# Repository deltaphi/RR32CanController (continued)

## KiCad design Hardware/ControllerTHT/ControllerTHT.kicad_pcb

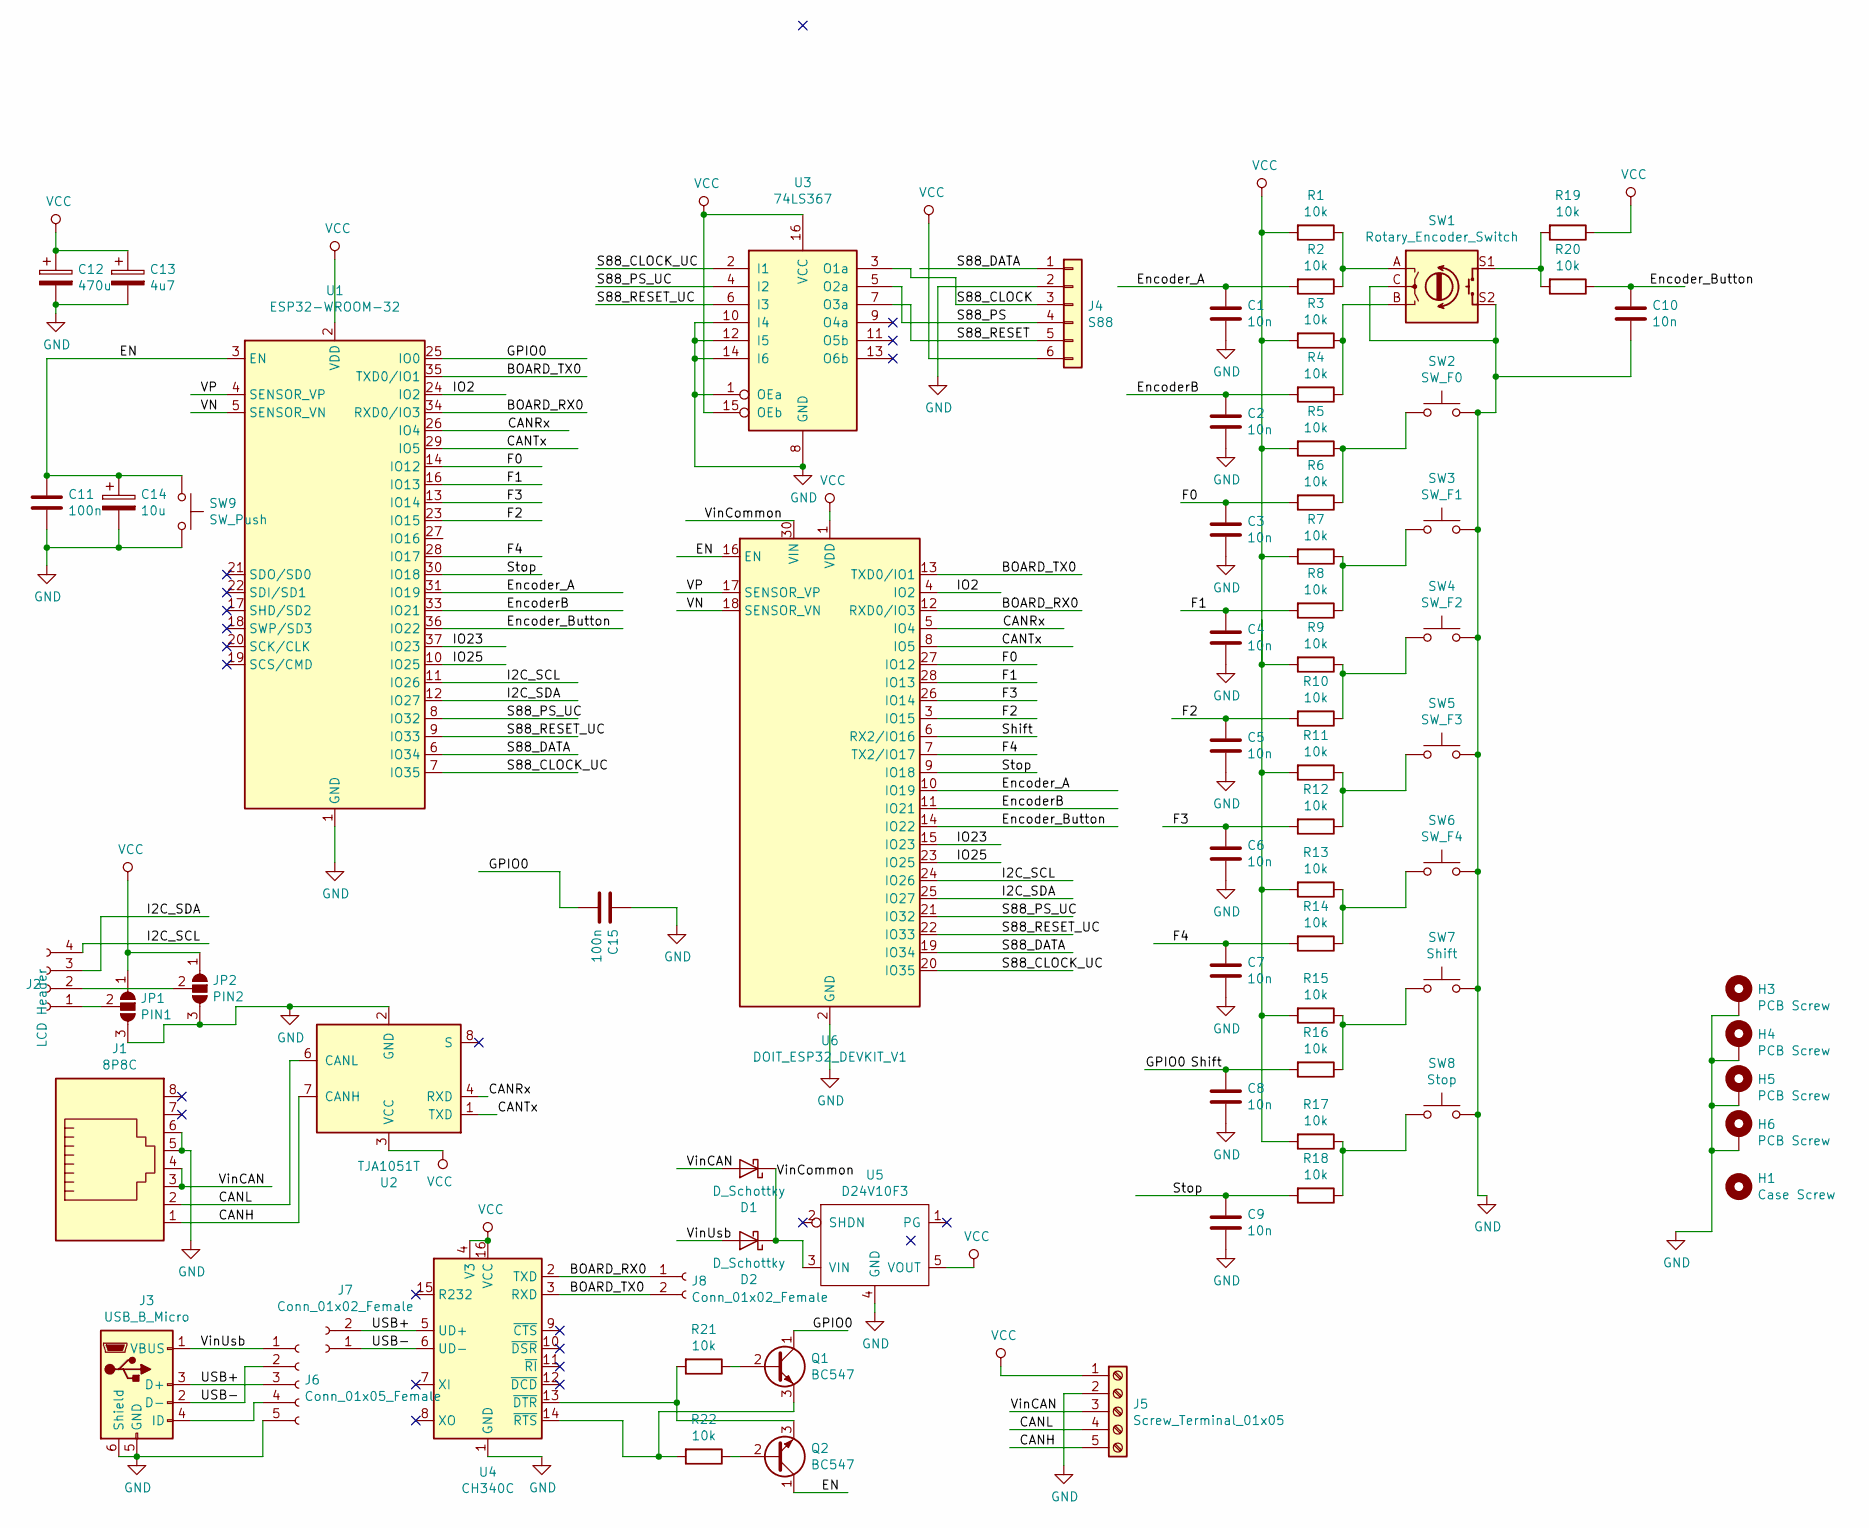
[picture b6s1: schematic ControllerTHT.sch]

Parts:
C1, C2, C3, C4, C5, C6, C7, C8, C9, C10: 10n; C_Disc_D3.4mm_W2.1mm_P2.50mm
C11, C15: 100n; C_Disc_D3.4mm_W2.1mm_P2.50mm
C12: 470u; CP_Radial_D10.0mm_P5.00mm
C13: 4u7; CP_Radial_D5.0mm_P2.50mm
C14: 10u; CP_Radial_D10.0mm_P5.00mm
D1, D2: D_Schottky; D_A-405_P7.62mm_Horizontal
H1: Case Screw; MountingHole_3.2mm_M3
H3, H4, H5, H6: PCB Screw; MountingHole_2.5mm_Pad_Via
J1: 8P8C; RJ45_Amphenol_54602-x08_Horizontal
J2: LCD Header; PinHeader_1x04_P2.54mm_Vertical
J3: USB_B_Micro; USB_Micro-B_Molex_47346-0001
J4: S88; PinHeader_1x06_P2.54mm_Horizontal
J5: Screw_Terminal_01x05; TerminalBlock_4Ucon_1x05_P3.50mm_Vertical
J6: Conn_01x05_Female; PinHeader_1x05_P2.54mm_Vertical
J7, J8: Conn_01x02_Female; PinHeader_1x02_P2.54mm_Vertical
JP1: PIN1; SolderJumper-3_P1.3mm_Open_Pad1.0x1.5mm_NumberLabels
JP2: PIN2; SolderJumper-3_P1.3mm_Open_Pad1.0x1.5mm_NumberLabels
Q1, Q2: BC547; TO-92_Inline
R1, R2, R3, R4, R5, R6, R7, R8, R9, R10, R11, R12, R13, R14, R15, R16, R17, R18, R19, R20, R21, R22: 10k; R_Axial_DIN0207_L6.3mm_D2.5mm_P10.16mm_Horizontal
SW1: Rotary_Encoder_Switch; RotaryEncoder_Alps_EC11E-Switch_Vertical_H20mm
SW2: SW_F0; SW_PUSH_6mm_H9.5mm
SW3: SW_F1; SW_PUSH_6mm_H9.5mm
SW4: SW_F2; SW_PUSH_6mm_H9.5mm
SW5: SW_F3; SW_PUSH_6mm_H9.5mm
SW6: SW_F4; SW_PUSH_6mm_H9.5mm
SW7: Shift; SW_PUSH_6mm_H9.5mm
SW8: Stop; SW_PUSH_6mm_H9.5mm
SW9: SW_Push; SW_PUSH_6mm
U1: ESP32-WROOM-32
U2: TJA1051T; SOIC-8_3.9x4.9mm_P1.27mm
U3: 74LS367; DIP-16_W7.62mm_Socket
U4: CH340C; SOIC-16_3.9x9.9mm_P1.27mm
U5: D24V10F3
U6: DOIT_ESP32_DEVKIT_V1; ESP32-DEVKITV1

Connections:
/BOARD_RX0: J8.1, U1.34 (RXD0/IO3), U4.2 (TXD), U6.12 (RXD0/IO3)
/BOARD_TX0: J8.2, U1.35 (TXD0/IO1), U4.3 (RXD), U6.13 (TXD0/IO1)
/CANH: J1.1, J5.5, U2.7 (CANH)
/CANL: J1.2, J5.4, U2.6 (CANL)
/CANRx: U1.26 (IO4), U2.4 (RXD), U6.5 (IO4)
/CANTx: U1.29 (IO5), U2.1 (TXD), U6.8 (IO5)
/EN: C11.1, C14.1, Q2.1 (C), SW9.1, U1.3 (EN), U6.16 (EN)
/EncoderB: C2.2, R4.2, U1.33 (IO21), U6.11 (IO21)
/Encoder_A: C1.2, R2.2, U1.31 (IO19), U6.10 (IO19)
/Encoder_Button: C10.2, R20.1, U1.36 (IO22), U6.14 (IO22)
/F0: C3.2, R6.2, U1.14 (IO12), U6.27 (IO12)
/F1: C4.2, R8.2, U1.16 (IO13), U6.28 (IO13)
/F2: C5.2, R10.2, U1.23 (IO15), U6.3 (IO15)
/F3: C6.2, R12.2, U1.13 (IO14), U6.26 (IO14)
/F4: C7.2, R14.2, U1.28 (IO17), U6.7 (TX2/IO17)
/GPIO0: C8.2, C15.2, Q1.1 (C), R16.2, U1.25 (IO0), U6.6 (RX2/IO16)
/I2C_SCL: J2.4, U1.11 (IO26), U6.24 (IO26)
/I2C_SDA: J2.3, U1.12 (IO27), U6.25 (IO27)
/IO2: U1.24 (IO2), U6.4 (IO2)
/IO23: U1.37 (IO23), U6.15 (IO23)
/IO25: U1.10 (IO25), U6.23 (IO25)
/S88_CLOCK: J4.3, U3.3 (O1a)
/S88_CLOCK_UC: U1.7 (IO35), U3.2 (I1), U6.20 (IO35)
/S88_DATA: J4.1, U1.6 (IO34), U6.19 (IO34)
/S88_PS: J4.4, U3.5 (O2a)
/S88_PS_UC: U1.8 (IO32), U3.4 (I2), U6.21 (IO32)
/S88_RESET: J4.5, U3.7 (O3a)
/S88_RESET_UC: U1.9 (IO33), U3.6 (I3), U6.22 (IO33)
/Stop: C9.2, R18.2, U1.30 (IO18), U6.9 (IO18)
/USB+: J3.3 (D+), J6.3, J7.2, U4.5 (UD+)
/USB-: J3.2 (D-), J6.2, J7.1, U4.6 (UD-)
/VN: U1.5 (SENSOR_VN), U6.18 (SENSOR_VN)
/VP: U1.4 (SENSOR_VP), U6.17 (SENSOR_VP)
/VinCAN: D1.2 (A), J1.3, J1.4, J5.3
/VinCommon: D1.1 (K), D2.1 (K), U5.3 (VIN), U6.30 (VIN)
/VinUsb: D2.2 (A), J3.1 (VBUS), J6.1
GND: C1.1, C2.1, C3.1, C4.1, C5.1, C6.1, C7.1, C8.1, C9.1, C10.1, C11.2, C12.2, C13.2, C14.2, C15.1, H3.1, H4.1, H5.1, H6.1, J1.5, J1.6, J3.5 (GND), J3.6 (Shield), J4.2, J5.2, J6.5, JP1.3 (B), JP2.3 (B), SW1.C, SW1.S2, SW2.2, SW3.2, SW4.2, SW5.2, SW6.2, SW7.2, SW8.2, SW9.2, U1.1 (GND), U1.15 (GND), U1.38 (GND), U2.2 (GND), U3.1 (OEa), U3.8 (GND), U3.10 (I4), U3.12 (I5), U3.14 (I6), U4.1 (GND), U5.4 (GND), U6.2 (GND), U6.29 (GND)
unnamed: J2.1, JP1.2 (C)
unnamed: J2.2, JP2.2 (C)
unnamed: J3.4 (ID), J6.4
unnamed: Q1.2 (B), R21.1
unnamed: Q1.3 (E), R22.2, U4.14 (~RTS)
unnamed: Q2.2 (B), R22.1
unnamed: Q2.3 (E), R21.2, U4.13 (~DTR)
unnamed: R1.1, R2.1, SW1.A
unnamed: R3.1, R4.1, SW1.B
unnamed: R5.1, R6.1, SW2.1
unnamed: R7.1, R8.1, SW3.1
unnamed: R9.1, R10.1, SW4.1
unnamed: R11.1, R12.1, SW5.1
unnamed: R13.1, R14.1, SW6.1
unnamed: R15.1, R16.1, SW7.1
unnamed: R17.1, R18.1, SW8.1
unnamed: R19.2, R20.2, SW1.S1
VCC: C12.1, C13.1, J4.6, J5.1, JP1.1 (A), JP2.1 (A), R1.2, R3.2, R5.2, R7.2, R9.2, R11.2, R13.2, R15.2, R17.2, R19.1, U1.2 (VDD), U2.3 (VCC), U3.15 (OEb), U3.16 (VCC), U4.4 (V3), U4.16 (VCC), U5.5 (VOUT), U6.1 (VDD)

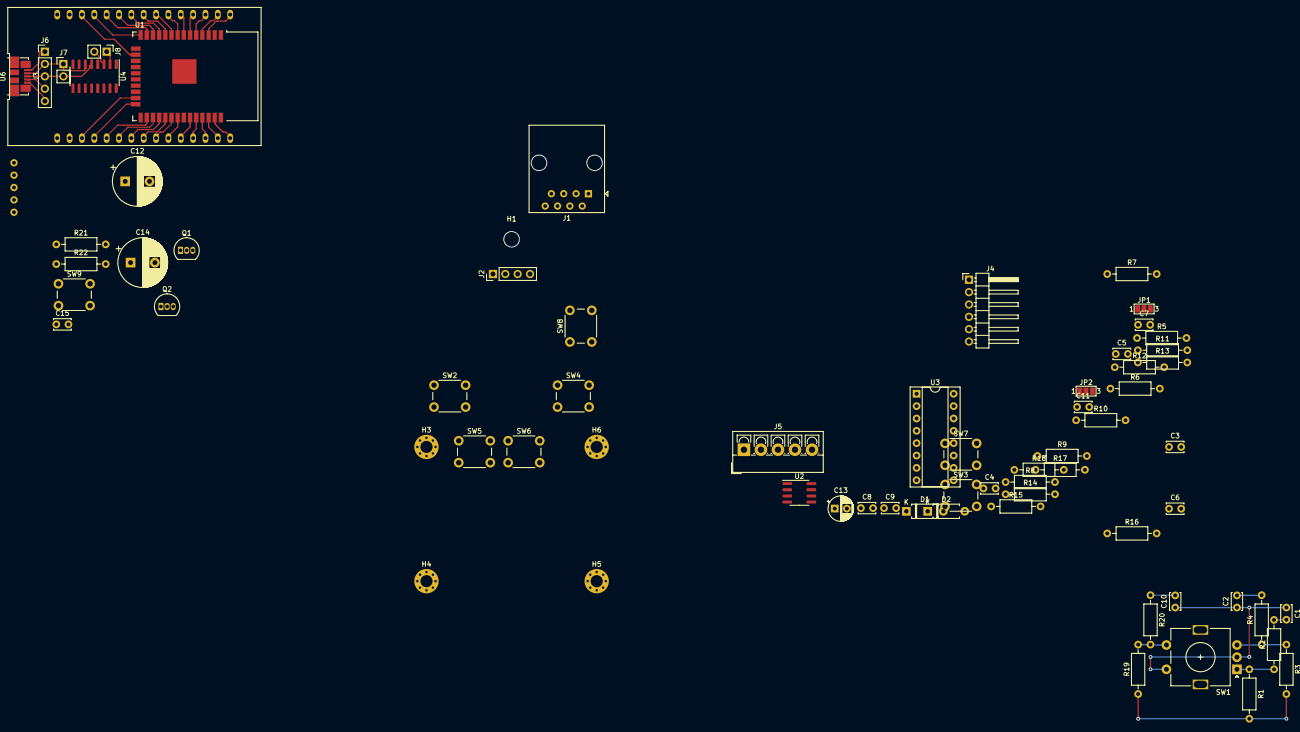
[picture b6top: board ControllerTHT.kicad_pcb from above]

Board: 2 copper layers, 71 parts (1 on the bottom side), 55 nets.

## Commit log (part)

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2018-12-30 Import of initial working prototype
2018-12-30 Fixed multi-turnouts
2019-02-07 Initial experiments with enabling the OLED display
2019-02-07 Fixed screen orientation
2019-02-07 Added RotaryEncoder Support
2019-02-13 Introduce some rudimentary structure.
2019-02-13 Display the Encoder value
2019-02-14 Fixed missing include
2019-02-14 Moved Display code to a separate class
2019-02-14 Improved output
2019-02-14 Request Loco Database
2019-02-15 Moved more code to the handler
2019-02-15 Moved sending CAN frames to the handler file
2019-02-15 Moved sending config data packets to handler
2019-02-15 Run clang-format on all the things
2019-02-16 Initial PCB
    An initial take at a PCB that can be mounted in the SP 2092 case.
    NOTE: The dimensions do not yet match!
2019-02-17 Updated fitting for SP 2090 enclosure
    Better fit, but still not perfect.
2019-02-17 Finished case-specific layout parts
2019-02-17 Added a first set of parts
2019-02-20 Added more parts
2019-02-20 Initial WiFi integration
    * Works for transmission, hardcoded to transmit via WiFi
    * Works for reception
    * Connecting to WiFi is unreliable
2019-02-21 Create an identifier from individual bytes
2019-02-21 Correctly use the send handler
2019-02-21 Fix commented code
2019-02-21 Added initial TextParser and a CMake configuration for UnitTesting
    * Downloads Google Test
    * Compiles selected sources and enables unit testing
    * Adapted apply-clang.sh to also format test case implementations
    * Initial set of bugfixes
2019-02-22 Improved BufferManager
2019-02-23 Fixed a compiler warning
2019-02-23 Initial non-working version of the TextParser
2019-02-23 Added findFirstOf for multiple characters
2019-02-23 Initial version of TextParser now working
2019-02-23 Ran clang-format
2019-02-23 Added Text parsing of incoming configuration data
    Configuration data is received and parsed. Currently, the identified tokens are dumped to the serial console only.
2019-02-24 Further renaming
2019-02-24 Added CRC functionality
2019-02-27 Added a script to create new class files
2019-02-27 Moved hash computation out of Identifier class
2019-02-27 Refactoring of types and constants
2019-02-27 Extended Identifier to allow for external hash computation
2019-02-27 Updated README with initial menuing design
2019-02-27 WIP: Added initial take on an Engine database
2019-02-28 Changed clang-format configuration to be Clang 6 compatible
    * Achieves compatibility with the build-in VS Code binary
2019-02-28 Clang-Format all the things
2019-02-28 WIP: Added more parts of the engine browser
2019-03-03 Rework on the file structure
2019-03-03 Refactoring to move parsing loknamen to other class
2019-03-03 More folder structuring
2019-03-03 Remove obsolete engine number
2019-03-03 Remove the need to erase the EngineBrowser each time
2019-03-03 Added helper function
2019-03-03 Added cursor support for the display
2019-03-03 Cursor-based browsing of engine list available
2019-03-03 Moved most message handling to Station class
2019-03-05 Switched to all-SMD Buttons
2019-03-08 Finished PCB
    * Reordered some pins to make the PCB layout easier
    * Added connector descriptions
    * Adjusted Silkscreen Items
2019-03-10 Updated USB Port
2019-03-12 Optimizations
    * Moved Screen connector to the other side
    * Optimized knee bends
2019-03-16 Fixed part footprints
2019-04-28 Made Caseness consistent
2019-04-28 Updated Gitignore
2019-04-28 Moved tests around. Set CPP standard for Tests to 17.
2019-05-19 Swap RX/TX
    Fixes #1
2019-05-26 Moved SMD controller prototype to separate folder
2019-05-26 Initial version of THT controller
2019-05-26 Added new Parts
2019-05-26 More tinkering with Footprints
2019-05-30 Intermediate steps
2019-05-30 Added an experimental ESP32 Breakout Board for Prototyping
2019-05-30 Fixup of holes and labels
2019-11-01 Improved comment
2019-11-01 Added switch for Display Flip
2019-11-01 Added default CNA pins
2019-11-01 Added preliminary support for local pushbuttons
2019-11-01 Switch menu when shift is pressed
2019-11-02 Add notification for functions
2019-11-02 UI Layout fix
2019-11-02 Improved comments
2019-11-02 Extracted Engine Direction Type
2019-11-02 Added option to conditionally set the name of the engine
    Avoids loosing the engine state in case the current engine was reselected.
2019-11-02 Extra logging
2019-11-02 Improfed end-of-stream handling
2019-11-03 Tinkered with logging
2019-11-03 Fix constant to pad with 0-bytes instead of spaces
2019-11-03 Fix requesting an engine
2019-11-03 Introduce EngineControl and initial download of Engine
2019-11-03 Fix scrolling through the engine list
2019-11-03 Fixed requesting the correct engine
2019-11-03 Removed unused variable
2019-11-03 Update to clang-format7
2019-11-04 Fix Friend Declarations
2019-11-04 More Logging
2019-11-05 Documentation improvements
2019-11-05 Removed useless includes
2019-11-05 Switch to ESP32-IDF CAN driver.
    This driver allows better buffer control.
2019-11-05 Added character push_back
2019-11-05 Added comments
2019-11-05 Run clang-format 7
2019-11-07 Display downloaded engine data
2019-11-07 Track engine speed & direction.
    Requests engine speed and direction when a new engine is selected. Updates display when another bus participant controls the engine.
2019-11-07 Send direction change/emergency stop
2019-11-08 Send and receive System Stop/Go
2019-11-08 Run clang-format
2019-11-08 Send and read function keys
2019-11-10 Upgraded the RotaryEncoder to 1.2.0
2019-11-10 Added Acceleration for the encoder in Engine Control mode.
    Actual acceleration values may require additional tweaking.
2019-11-10 Remove warnings
2019-11-10 Start refactoring towards MVC
2019-11-13 Added header guards
2019-11-13 Massive refactoring to something at least remotely representing an MVC architecture.
2019-11-13 Refactoring of names
2019-11-13 Formatting
2019-11-14 Updated RotaryEncoder to new release
2019-11-23 Updated AsyncShiftIn library
2019-11-23 Added support for SH1106 displays
2019-11-23 Integrated original TurnoutControl into MVC design.
2019-11-24 WIP: Moved TurnoutTypes to model
2019-11-24 WIP: Added runtime-modifiable button map
2019-11-24 Additional typedefs and constants.
2019-11-24 Useful functionality.
2019-11-24 Runtime-remapping of buttons now works
2019-11-26 Converted LocoList to use the abstract menu.
2019-11-29 Moved CAN stuff to separate class in preparation for WiFi merge
2019-11-29 Additional fixes
2019-11-30 Iniitalize Turnout buttons to inverted state.
    Fixes #4.
2019-11-30 Reduced CAN transmission timeout to 100ms
2019-11-30 Foce-Update the LocoList menu on entering.
    Fixes #5.
2019-11-30 Fix engine speed not being recoreded correctly on emergency stop
2019-11-30 Made WiFi functionality configurable
2019-11-30 Fix selected item on entrance to menu
2019-12-01 Removed obsolete lookup
2019-12-01 Resolve off-by-one in turnout mapping.
2019-12-01 Force all stored mappings to be SingleTurnout.
    ActionLists are currently not supported.
2019-12-01 Added a function to print turnout mappging entries
2019-12-07 Added easy switch for multiple hardware confguations
2019-12-14 Added ChangeLog
2019-12-14 Fix detecting packages on WiFi
2019-12-15 Applied clang-format
2019-12-15 Add a second task to drive the console library.
2019-12-15 Added switching turnouts via serial
2019-12-15 Added serial access to ActionLists.
2019-12-15 Added ActionLists accessible via serial.
2019-12-15 Better use of conversion templates
2019-12-15 Introduced NewType for TurnoutAddresses.
2019-12-16 Fix prints and includes
2019-12-16 Full support for ActionLists.
2019-12-22 Serialized Aciton Lists during printout
2019-12-27 Added a PCB for an S88 switchboard.
2019-12-27 Fixes.
2019-12-27 Fixed positioning of switches
2019-12-27 More position fixes.
2019-12-27 Converted mounting holes to vias
2019-12-28 Added a Breakout for an HCT367
2019-12-29 Fixes on the breakout board
2019-12-29 Added gerber folders to gitignore
2019-12-29 Updates projects for manufacturing
2019-12-29 Further updates
2019-12-29 Fixed IC footprints
2019-12-30 Route configuration Requests via UDP, everything else via TCP.
2019-12-30 Fix duplicate transmission of garbage packets via UDP
2020-01-01 Added LocoCard Breakout
2020-01-07 Rounded Corners
2020-02-16 Enable non-destructive reading of edges
2020-02-17 Fix wrong pin assignment
2020-02-17 Made CAN optional
2020-02-17 More debug output
2020-05-14 Converted RR32Can to external library
2020-05-15 Formatting yadda-yadda
2020-05-15 Moved ConsoleApplications to applications subdirectory
2020-05-15 Split UIAssets in HAL and Application Part
2020-05-15 Refactor DisplayManager in application and HAL part
2020-05-15 Moved InputState to application
2020-05-15 Split Settings in HAL/App
2020-05-15 Moved ActionList Model
2020-05-15 Move actionList memory to model
2020-05-15 Moved ActionListProcessor to application
2020-05-15 Refactored TurnoutMap
2020-05-15 Moved Utility Classes
2020-05-15 Moved all controllers to application
2020-05-15 Intermediate State preparing for unit testing
2020-05-15 Enabled Unit Testing
    * Upgraded to new version of RR32CanLibrary
2020-05-15 Added missing pure virtual
2020-05-15 Added first sensible unit test
2020-05-16 Fixed pointer assignment.
2020-05-16 Added debugger configuration
2020-05-16 Create main.yml
    Start using GitHub Actions based on the template file.
2020-05-16 clang-format fixes
2020-05-16 Extended Workflow
2020-05-16 Reworked Action
2020-05-16 Reworked workflow
2020-05-16 More Actions
2020-05-16 Switch from Ninja to make
2020-05-16 Examine environment
2020-05-16 Switched to GCC8
2020-05-16 Relax C++ version requirements to make CMake happy
2020-05-16 Remove non-working compiler selection
2020-05-16 Check out submodules
2020-05-16 Clenaup master job
2020-05-16 Add support for PlatformIO
2020-05-16 Fix PlatformIO parameters
2020-05-16 Copy WiFi config
2020-05-16 Added windows test build
2020-05-16 Fixed path
2020-05-16 Fixed typos
2020-05-16 Updated Badges
2020-05-16 Attempt to fix badges
2020-05-17 Exclude Argtable
2020-05-17 Updated .clang-format for Clang Format 10
2020-05-17 Adjust to 100 column limit
    Limit chosen so that lines are fully visible in the VS Code Diff View on a Full-HD laptop display.
2020-05-17 Some fixes to GPIO-based input
2020-05-17 Fixed Pin assignment
2020-05-17 Collect old bits of changes
2020-05-19 Fix status badges
2020-05-28 Updated to latest RR32Can Library
2020-06-07 Removed submodules
2020-06-07 Bump library version
2020-06-07 Removed submodule
2020-06-07 Removed unneeded typedefs
2020-06-07 Removed use of C++ features to make VS 2019 and Googletest play together nicely.
2020-06-21 Fixed inverted power connections for shift register
2020-06-28 Extend gitignore for VS Code CMake
2020-06-28 Updated to new RR32CanLibrary
2021-12-17 Fixed Platform version
2021-12-17 Remove AsyncShiftIn Submodule
2021-12-17 Update CI config for PIO libraries
2021-12-17 Fix library reference
2021-12-18 Fix include paths
2021-12-19 Initial port to arduinoesp32-2.0
2021-12-19 Pin version of the platform package
2021-12-19 Upgrade to C++17
2021-12-19 Execute workflows under more conditions
2021-12-19 Even more conditions
2021-12-19 Fix no-branch slectivity
2021-12-19 Allow manual workflow execution
2021-12-20 Update to lates RR32CanLibrary
    * Made all the easy fixes, the hard ones are still missing.
2021-12-20 Migrate back to working condition
2021-12-20 Fix Tests and Compiler Support
2021-12-24 Convert function download to state machine
    Avoids overloading the Gleisbox by spreading out requests over time.
2022-01-07 Split HArdware Revision to separate configurations
2022-01-07 Add missing rename
2022-01-07 Fixing paths and parameters
2022-01-07 Fix misnamed define
2024-12-31 Ignore .DS_Store files
2025-08-28 Add Measurements
2025-08-28 Updated to v1.3 for manufacturing
2025-08-28 Fix VCC/GND assignment
2025-08-28 JLCPCB Plugin Data
2025-08-28 Updated JLCPCB DRC
2025-08-28 Center connectors
2025-08-28 Added Production Files
2025-08-30 Updated production files
2025-08-31 Update Library Versions
    Compile/Link test works, no runtime test, yet.
2025-08-31 Update CI Job to VS 2022
2025-08-31 Update CMake Action on Windows
2025-08-31 Add CMake Presets
